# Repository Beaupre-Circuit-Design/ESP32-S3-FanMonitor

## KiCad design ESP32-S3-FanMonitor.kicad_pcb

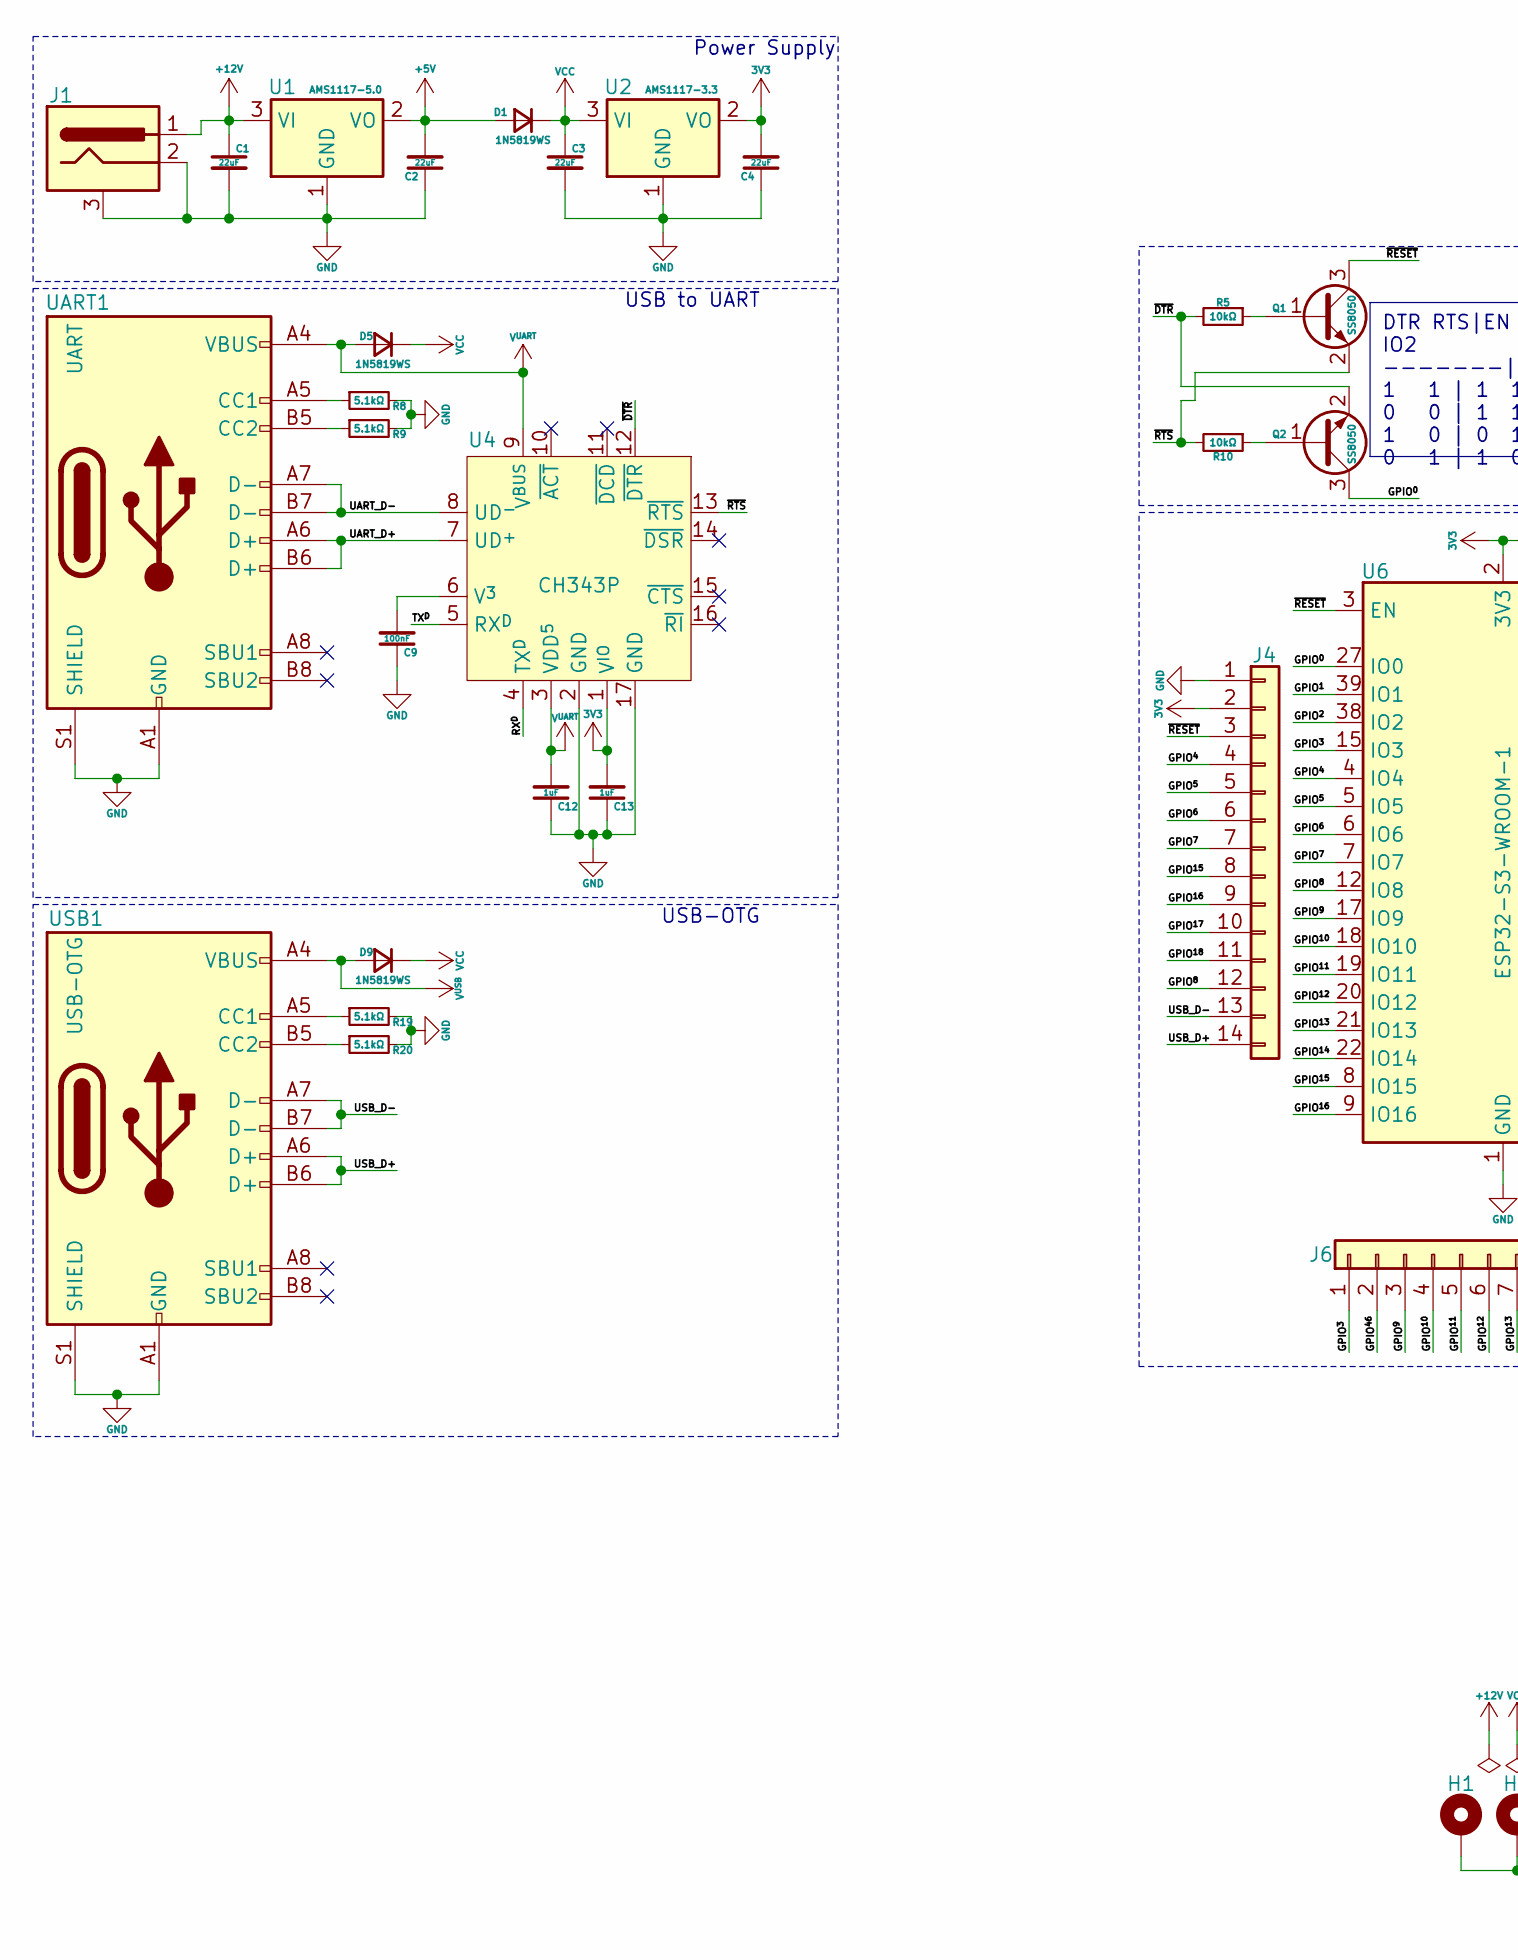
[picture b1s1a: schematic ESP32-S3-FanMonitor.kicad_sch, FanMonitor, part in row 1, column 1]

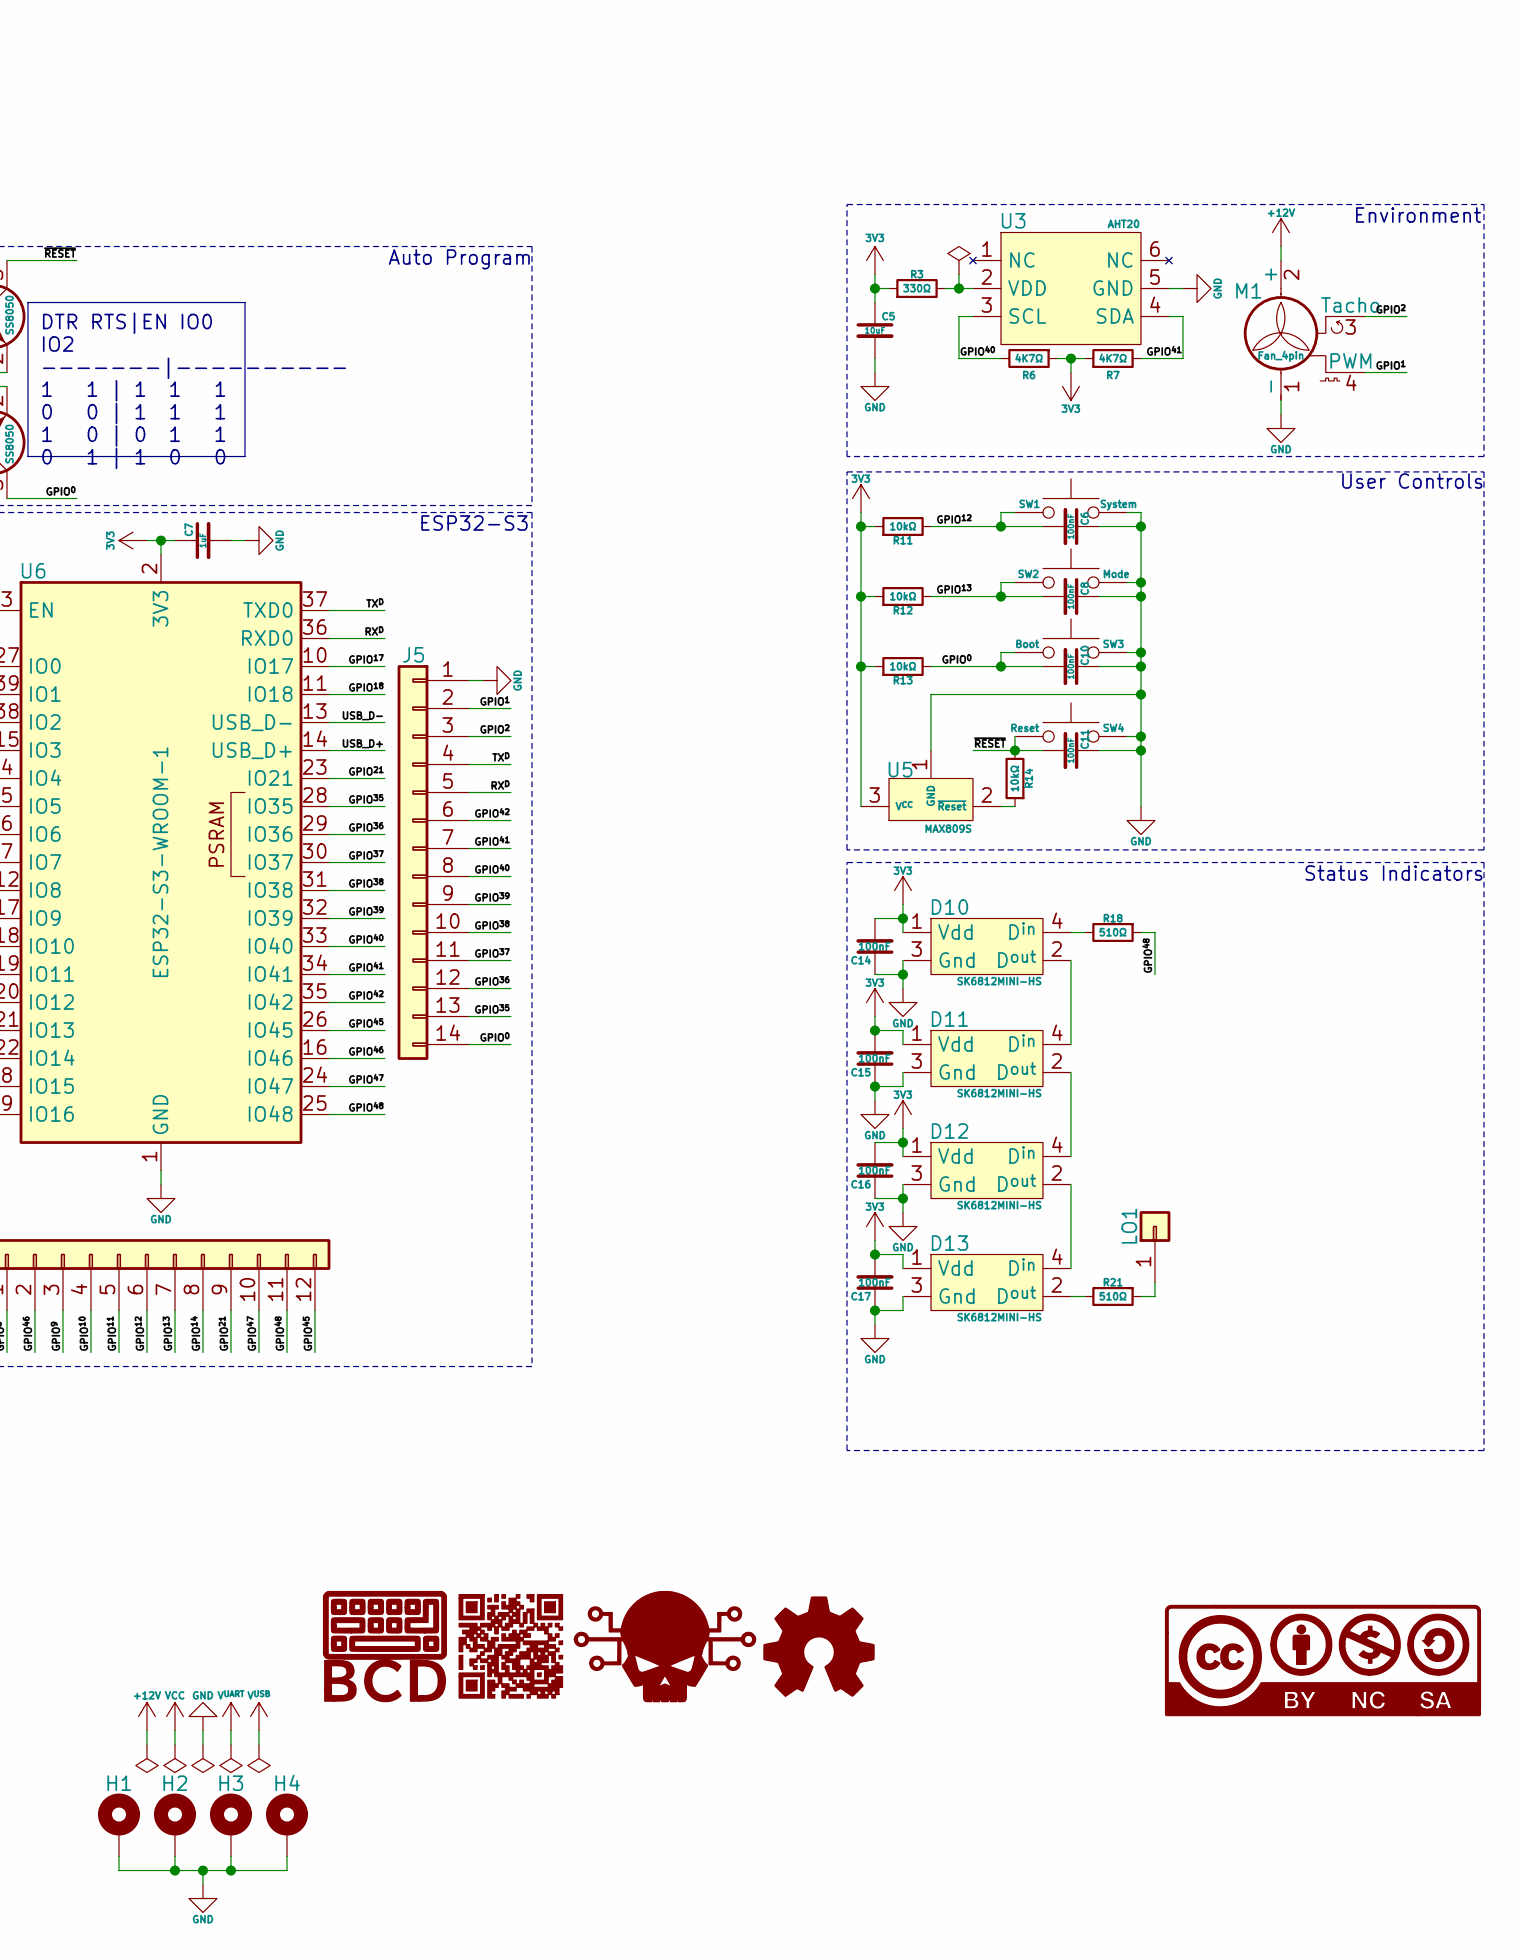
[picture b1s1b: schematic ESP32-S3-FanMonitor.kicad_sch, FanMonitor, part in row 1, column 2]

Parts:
C1, C2, C3, C4: 22uF; C_0805_2012Metric; PartNumber CL21A226MAQNNNE; JLCPCB C45783
C5: 10uF; C_0603_1608Metric; PartNumber CL10A106MA8NRNC; JLCPCB C96446
C6, C8, C9, C10, C11, C14, C15, C16, C17: 100nF; C_0402_1005Metric; PartNumber CL05B104KO5NNNC; JLCPCB C1525
C7, C12, C13: 1uF; C_0402_1005Metric; PartNumber CL05A105KA5NQNC; JLCPCB C52923
D1, D5, D9: 1N5819WS; D_SOD-323; PartNumber 1N5819WS; JLCPCB C191023
D10, D11, D12, D13: SK6812MINI-HS; PartNumber SK6812MINI-HS; JLCPCB C2922787
G1: BCD_Logo; BCD_Logo_2.5mm
G2: BDC_QR; BDC_QR_2.5mm
G3: Skull; Skull_2.5mm
G4: OpenSource_Hardware; Open_Source_Hardware_2.5mm
G5: CC-BY-NC-SA; cc-by-nc-sa_2.5mm
H1, H2, H3, H4: MountingHole_Pad; MountingHole_3.5mm_Pad_Via
J1: Barrel_Jack_MountingPin; BarrelJack_Horizontal
J4, J5: Conn_01x14; PinHeader_1x14_P1.27mm_Vertical
J6: Conn_01x12; PinHeader_1x12_P1.27mm_Vertical
LO1: Conn_01x01; PinHeader_1x01_P1.27mm_Vertical
M1: Fan_4pin; FanPinHeader_1x04_P2.54mm_Vertical
Q1, Q2: SS8050; SOT-23; PartNumber SS8050(RANGE:200-350); JLCPCB C2150
R3: 330Ω; R_0402_1005Metric; PartNumber 0402WGF3300TCE; JLCPCB C25104
R5, R10, R11, R12, R13, R14: 10kΩ; R_0402_1005Metric; PartNumber 0402WGF1002TCE; JLCPCB C25744
R6, R7: 4K7Ω; R_0402_1005Metric; PartNumber 0402WGF4701TCE; JLCPCB C25900
R8, R9, R19, R20: 5.1kΩ; R_0402_1005Metric; PartNumber 0402WGF5101TCE; JLCPCB C25905
R18, R21: 510Ω; R_0402_1005Metric; PartNumber 0402WGF5100TCE; JLCPCB C25123
SW1: System; SW_Push_1P1T_XKB_TS-1187A; PartNumber TS-1187A-B-A-B; JLCPCB C318884
SW2: Mode; SW_Push_1P1T_XKB_TS-1187A; PartNumber TS-1187A-B-A-B; JLCPCB C318884
SW3: Boot; SW_Push_1P1T_XKB_TS-1187A; PartNumber TS-1187A-B-A-B; JLCPCB C318884
SW4: Reset; SW_Push_1P1T_XKB_TS-1187A; PartNumber TS-1187A-B-A-B; JLCPCB C318884
U1: AMS1117-5.0; SOT-223-3_TabPin2; PartNumber AMS1117-5.0; JLCPCB C6187
U2: AMS1117-3.3; SOT-223-3_TabPin2; PartNumber AMS1117-3.3; JLCPCB C6186
U3: AHT20; PartNumber AHT20; JLCPCB C2757850
U4: CH343P; QFN-16-1EP_3x3mm_P0.5mm_EP1.7x1.7mm; PartNumber CH343P; JLCPCB C2846043
U5: MAX809S; SOT-23; PartNumber MAX809S; JLCPCB C347371
U6: ESP32-S3-WROOM-1; ESP32-S3-WROOM-1_HandSoldering; PartNumber ESP32-S3-WROOM-1-N16R8; JLCPCB C2913202
UART1: UART; USB_C_Receptacle_HRO_TYPE-C-31-M-12; PartNumber TYPE-C-31-M-12; JLCPCB C165948
USB1: USB-OTG; USB_C_Receptacle_HRO_TYPE-C-31-M-12; PartNumber TYPE-C-31-M-12; JLCPCB C165948

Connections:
3V3: C4.2, C5.1, C7.1, C13.2, C14.2, C15.2, C16.2, C17.2, D10.1 (Vdd), D11.1 (Vdd), D12.1 (Vdd), D13.1 (Vdd), J4.2, R3.1, R6.1, R7.1, R11.1, R12.1, R13.1, U2.2 (VO), U4.1 (V^{IO}), U5.3 (V^{CC}), U6.2 (3V3)
+5V: C2.2, D1.2 (A), U1.2 (VO)
+12V: C1.1, J1.1, M1.2 (+), U1.3 (VI)
/GPIO^{0}: C10.2, J5.14, Q2.3 (C), R13.2, SW3.2, U6.27 (IO0)
/GPIO^{1}: J5.2, M1.4 (PWM), U6.39 (IO1)
/GPIO^{2}: J5.3, M1.3 (Tacho), U6.38 (IO2)
/GPIO^{3}: J6.1, U6.15 (IO3)
/GPIO^{4}: J4.4, U6.4 (IO4)
/GPIO^{5}: J4.5, U6.5 (IO5)
/GPIO^{6}: J4.6, U6.6 (IO6)
/GPIO^{7}: J4.7, U6.7 (IO7)
/GPIO^{8}: J4.12, U6.12 (IO8)
/GPIO^{9}: J6.3, U6.17 (IO9)
/GPIO^{10}: J6.4, U6.18 (IO10)
/GPIO^{11}: J6.5, U6.19 (IO11)
/GPIO^{12}: C6.2, J6.6, R11.2, SW1.2, U6.20 (IO12)
/GPIO^{13}: C8.2, J6.7, R12.2, SW2.2, U6.21 (IO13)
/GPIO^{14}: J6.8, U6.22 (IO14)
/GPIO^{15}: J4.8, U6.8 (IO15)
/GPIO^{16}: J4.9, U6.9 (IO16)
/GPIO^{17}: J4.10, U6.10 (IO17)
/GPIO^{18}: J4.11, U6.11 (IO18)
/GPIO^{21}: J6.9, U6.23 (IO21)
/GPIO^{35}: J5.13, U6.28 (IO35)
/GPIO^{36}: J5.12, U6.29 (IO36)
/GPIO^{37}: J5.11, U6.30 (IO37)
/GPIO^{38}: J5.10, U6.31 (IO38)
/GPIO^{39}: J5.9, U6.32 (IO39)
/GPIO^{40}: J5.8, R6.2, U3.3 (SCL), U6.33 (IO40)
/GPIO^{41}: J5.7, R7.2, U3.4 (SDA), U6.34 (IO41)
/GPIO^{42}: J5.6, U6.35 (IO42)
/GPIO^{45}: J6.12, U6.26 (IO45)
/GPIO^{46}: J6.2, U6.16 (IO46)
/GPIO^{47}: J6.10, U6.24 (IO47)
/GPIO^{48}: J6.11, R18.1, U6.25 (IO48)
/RX^{D}: J5.5, U4.4 (TX^{D}), U6.36 (RXD0)
/TX^{D}: J5.4, U4.5 (RX^{D}), U6.37 (TXD0)
/UART_D+: U4.7 (UD^{+}), UART1.A6 (D+), UART1.B6 (D+)
/UART_D-: U4.8 (UD^{-}), UART1.A7 (D-), UART1.B7 (D-)
/USB_D+: J4.14, U6.14 (USB_D+), USB1.A6 (D+), USB1.B6 (D+)
/USB_D-: J4.13, U6.13 (USB_D-), USB1.A7 (D-), USB1.B7 (D-)
/~DTR: Q2.2 (E), R5.2, U4.12 (~DTR)
/~RESET: C11.2, J4.3, Q1.3 (C), R14.2, SW4.2, U6.3 (EN)
/~RTS: Q1.2 (E), R10.2, U4.13 (~RTS)
GND: C1.2, C2.1, C3.2, C4.1, C5.2, C6.1, C7.2, C8.1, C9.1, C10.1, C11.1, C12.1, C13.1, C14.1, C15.1, C16.1, C17.1, D10.3 (Gnd), D11.3 (Gnd), D12.3 (Gnd), D13.3 (Gnd), H1.1, H2.1, H3.1, H4.1, J1.2, J1.3 (MountPin), J4.1, J5.1, M1.1 (-), R8.2, R9.2, R19.2, R20.2, SW1.1, SW2.1, SW3.1, SW4.1, U1.1 (GND), U2.1 (GND), U3.5 (GND), U4.2 (GND), U4.17 (GND), U5.1 (GND), U6.1 (GND), U6.40 (GND), U6.41 (GND), UART1.A1 (GND), UART1.A12 (GND), UART1.B1 (GND), UART1.B12 (GND), UART1.S1 (SHIELD), USB1.A1 (GND), USB1.A12 (GND), USB1.B1 (GND), USB1.B12 (GND), USB1.S1 (SHIELD)
unnamed: D10.4 (D^{in}), R18.2
unnamed: D10.2 (D^{out}), D11.4 (D^{in})
unnamed: D11.2 (D^{out}), D12.4 (D^{in})
unnamed: D12.2 (D^{out}), D13.4 (D^{in})
unnamed: D13.2 (D^{out}), R21.2
unnamed: LO1.1, R21.1
unnamed: Q1.1 (B), R5.1
unnamed: Q2.1 (B), R10.1
unnamed: R3.2, U3.2 (VDD)
unnamed: C9.2, U4.6 (V^{3})
unnamed: R14.1, U5.2 (~Reset)
unnamed: R8.1, UART1.A5 (CC1)
unnamed: R9.1, UART1.B5 (CC2)
unnamed: R19.1, USB1.A5 (CC1)
unnamed: R20.1, USB1.B5 (CC2)
VCC: C3.1, D1.1 (K), D5.1 (K), D9.1 (K), U2.3 (VI)
V^{UART}: C12.2, D5.2 (A), U4.3 (VDD^{5}), U4.9 (V^{BUS}), UART1.A4 (VBUS), UART1.A9 (VBUS), UART1.B4 (VBUS), UART1.B9 (VBUS)
V^{USB}: D9.2 (A), USB1.A4 (VBUS), USB1.A9 (VBUS), USB1.B4 (VBUS), USB1.B9 (VBUS)

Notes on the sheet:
DTR RTS|EN IO0 IO2 -------|---------- 1 1 | 1 1 1 0 0 | 1 1 1 1 0 | 0 1 1 0 1 | 1 0 0
User Controls
ESP32-S3
Power Supply
Status Indicators
USB-OTG
USB to UART
Environment
Auto Program

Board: 4 copper layers, 68 parts (5 on the bottom side), 63 nets, no tracks yet.
